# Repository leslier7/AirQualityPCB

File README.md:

# Air Quality PCB

A custom air quality monitoring device with an ESP32-C3 microcontroller, designed to measure environmental sensor data and transmit it over WiFi and LoRa.

## Repository Structure

```
AirQualityPCB/
├── PCB/        # KiCad schematic, layout, BOM, and fabrication outputs
└── Firmware/   # PlatformIO firmware for the ESP32-C3
```

## PCB

The PCB was designed in KiCad and lives in the [PCB/](PCB/) folder. This folder contains the schematic, board layout, and a custom component library (3D models, footprints, and symbols).

The BOM, STEP file, and Gerbers can be found on the [GitHub Releases](https://github.com/leslier7/AirQualityPCB/releases) page. They can also be extracted from the KiCAD project.

## Firmware

The firmware is written in C++ using the PlatformIO build system and targets the ESP32-C3.

For instructions on setting up the development environment, building, and flashing the firmware, see [Firmware/README.md](Firmware/README.md).

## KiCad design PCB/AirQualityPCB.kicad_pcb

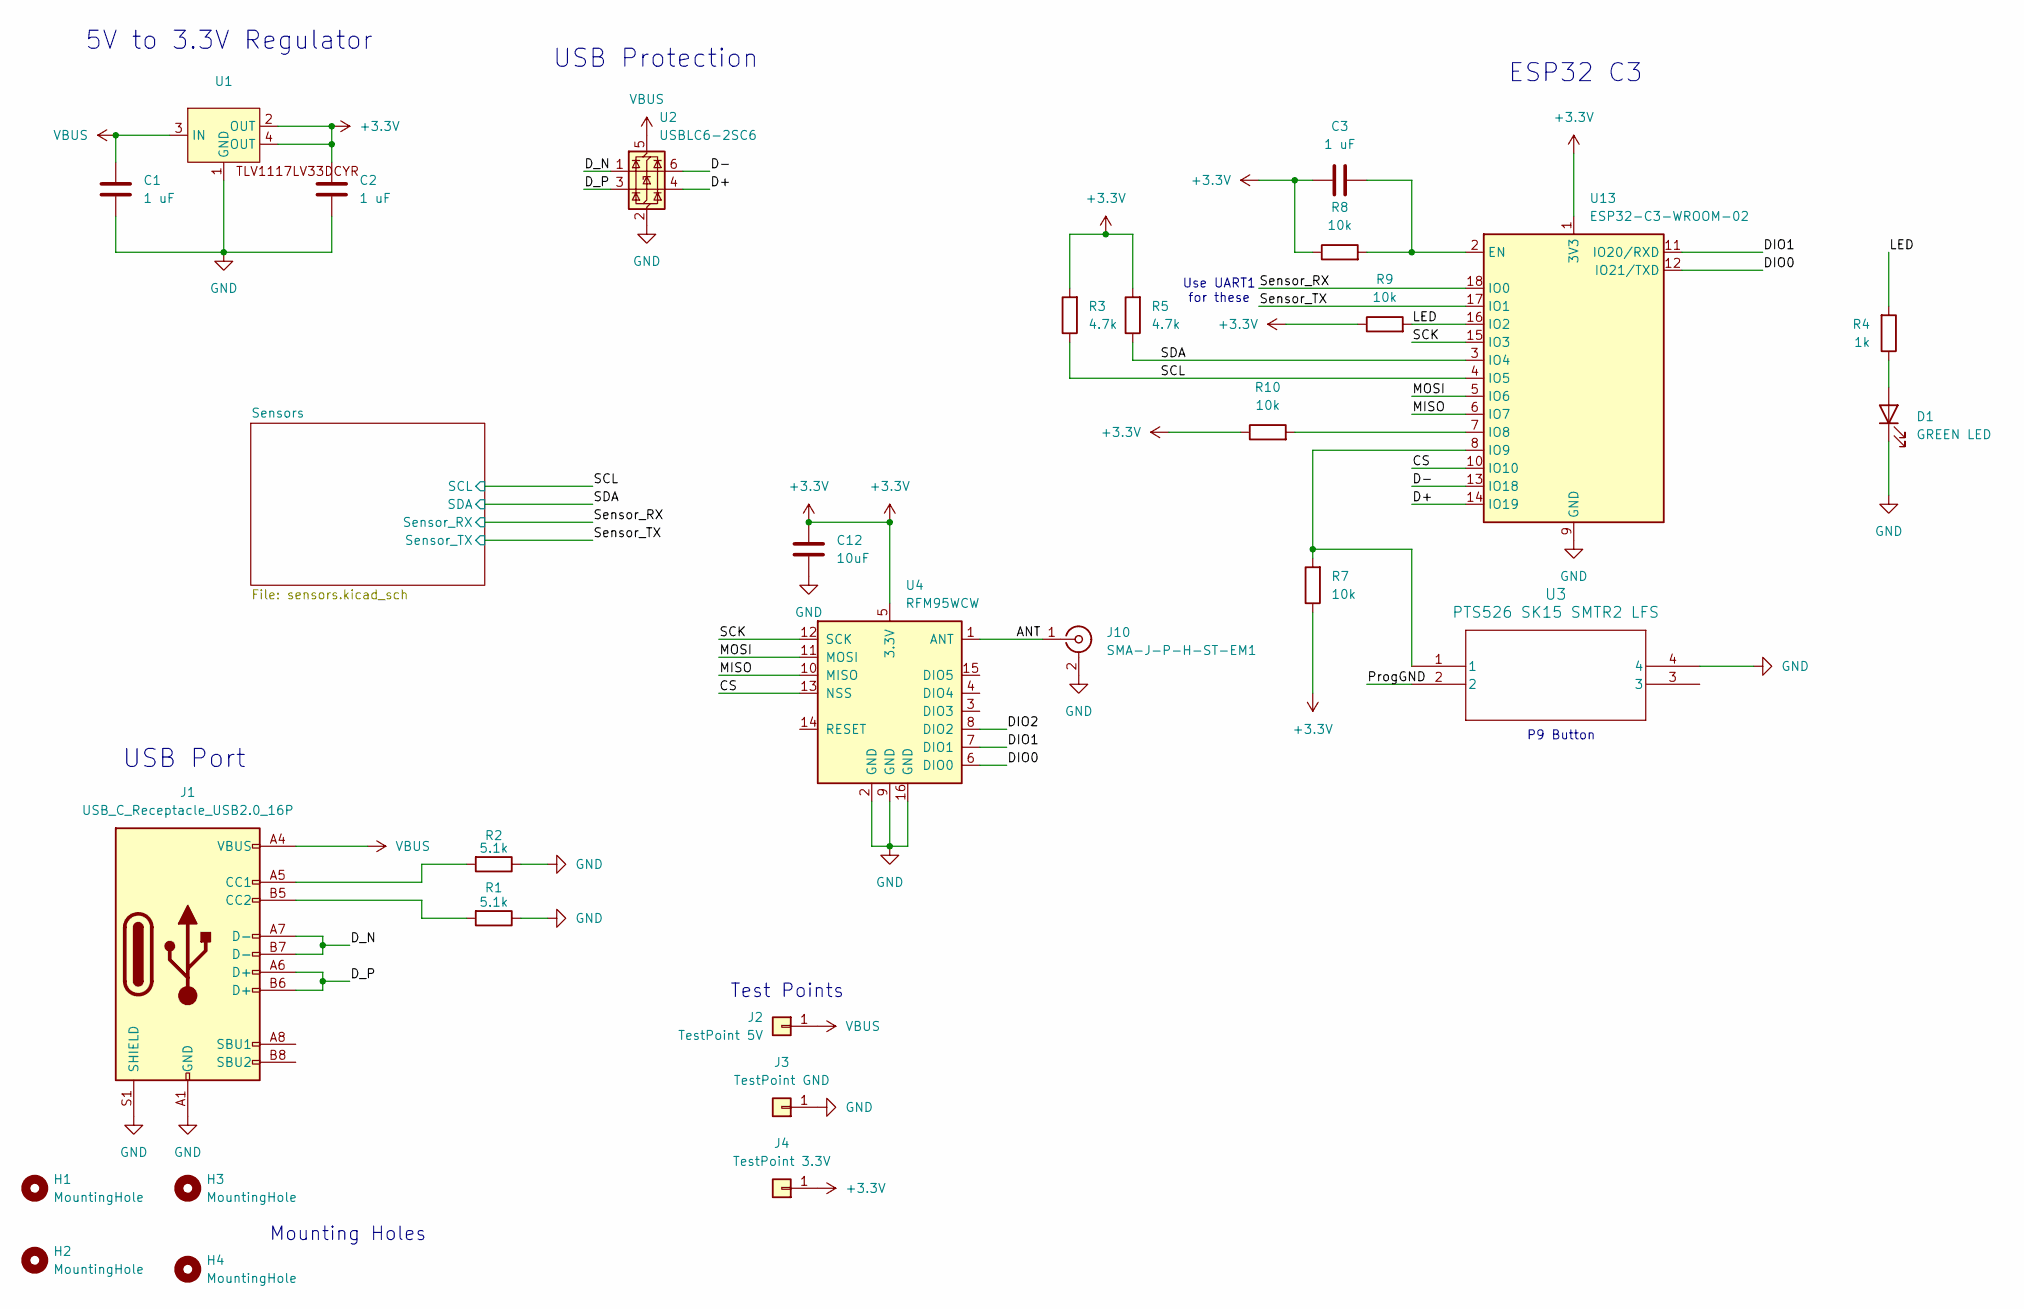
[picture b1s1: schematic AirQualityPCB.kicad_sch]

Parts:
C1, C2, C3: 1 uF; C_1206_3216Metric; Manufacturer Part Number CL31B105KCHNNNE
C12: 10uF; C_1206_3216Metric; Manufacturer Part Number TMK316BJ106KL-T
D1: GREEN LED; LED_1206_3216Metric; Manufacturer Part Number HSMG-C150
H1, H2, H3, H4: MountingHole; MountingHole_3.2mm_M3_ISO7380_Pad
J1: USB_C_Receptacle_USB2.0_16P; USB_C_Receptacle_GCT_USB4105-xx-A_16P_TopMnt_Horizontal; Manufacturer Part Number USB4105-GF-A
J2: TestPoint 5V; TestPoint_Pad_D1.0mm
J3: TestPoint GND; TestPoint_Pad_D1.0mm
J4: TestPoint 3.3V; TestPoint_Pad_D1.0mm
J10: SMA-J-P-H-ST-EM1; SMA_Samtec_SMA-J-P-H-ST-EM1_EdgeMount; Manufacturer Part Number SMA-J-P-H-ST-EM1
R1, R2: 5.1k; R_1206_3216Metric; Manufacturer Part Number CRCW12065K10FKEA
R3, R5: 4.7k; R_1206_3216Metric; Manufacturer Part Number RT1206FRE074K7L
R4: 1k; R_1206_3216Metric; Manufacturer Part Number RC1206FR-071KL
R7, R8, R9, R10: 10k; R_0805_2012Metric; Manufacturer Part Number RR1220P-103-D
U1: Regulator; SOT-223; Manufacturer Part Number TLV1117LV33DCYR
U2: USBLC6-2SC6; SOT-23-6; Manufacturer Part Number USBLC6-2SC6
U3: PTS526 SK15 SMTR2 LFS; PTS526SK15SMTR2 LFS; Manufacturer Part Number PTS526SK15SMTR2 LFS
U4: RFM95WCW; HOPERF_RFM9XW_SMD; Manufacturer Part Number COM-18085
U13: ESP32-C3-WROOM-02; Manufacturer Part Number ESP32-C3-WROOM-02-N4

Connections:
+3.3V: C2.2, C3.1, C12.2, J4.1, R3.2, R5.2, R7.1, R8.1, R9.1, R10.1, U1.2 (OUT), U1.4 (OUT), U4.5 (3.3V), U13.1 (3V3); also elsewhere on the board
/ANT: J10.1 (In), U4.1 (ANT)
/CS: U4.13 (NSS), U13.10 (IO10)
/D+: U2.4 (I/O2), U13.14 (IO19)
/D-: U2.6 (I/O1), U13.13 (IO18)
/DIO0: U4.6 (DIO0), U13.12 (IO21/TXD)
/DIO1: U4.7 (DIO1), U13.11 (IO20/RXD)
/DIO2: U4.8 (DIO2)
/D_N: J1.A7 (D-), J1.B7 (D-), U2.1 (I/O1)
/D_P: J1.A6 (D+), J1.B6 (D+), U2.3 (I/O2)
/LED: R4.2, R9.2, U13.16 (IO2)
/MISO: U4.10 (MISO), U13.6 (IO7)
/MOSI: U4.11 (MOSI), U13.5 (IO6)
/ProgGND: U3.2
/SCK: U4.12 (SCK), U13.15 (IO3)
/SCL: R3.1, U13.4 (IO5); also elsewhere on the board
/SDA: R5.1, U13.3 (IO4); also elsewhere on the board
/Sensor_RX: U13.18 (IO0); also elsewhere on the board
/Sensor_TX: U13.17 (IO1); also elsewhere on the board
GND: C1.1, C2.1, C12.1, D1.1 (K), J1.A1 (GND), J1.A12 (GND), J1.B1 (GND), J1.B12 (GND), J1.S1 (SHIELD), J3.1, J10.2 (Ext), R1.1, R2.1, U1.1 (GND), U2.2 (GND), U3.4, U4.2 (GND), U4.9 (GND), U4.16 (GND), U13.9 (GND), U13.19 (GND); also elsewhere on the board
unnamed: D1.2 (A), R4.1
unnamed: J1.A5 (CC1), R2.2
unnamed: J1.B5 (CC2), R1.2
unnamed: C3.2, R8.2, U13.2 (EN)
unnamed: R10.2, U13.7 (IO8)
unnamed: R7.2, U3.1, U13.8 (IO9)
VBUS: C1.2, J1.A4 (VBUS), J1.A9 (VBUS), J1.B4 (VBUS), J1.B9 (VBUS), J2.1, U1.3 (IN), U2.5 (VBUS)

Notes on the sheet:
USB Protection
5V to 3.3V Regulator
Test Points
Use UART1 for these
Mounting Holes
P9 Button
ESP32 C3
USB Port

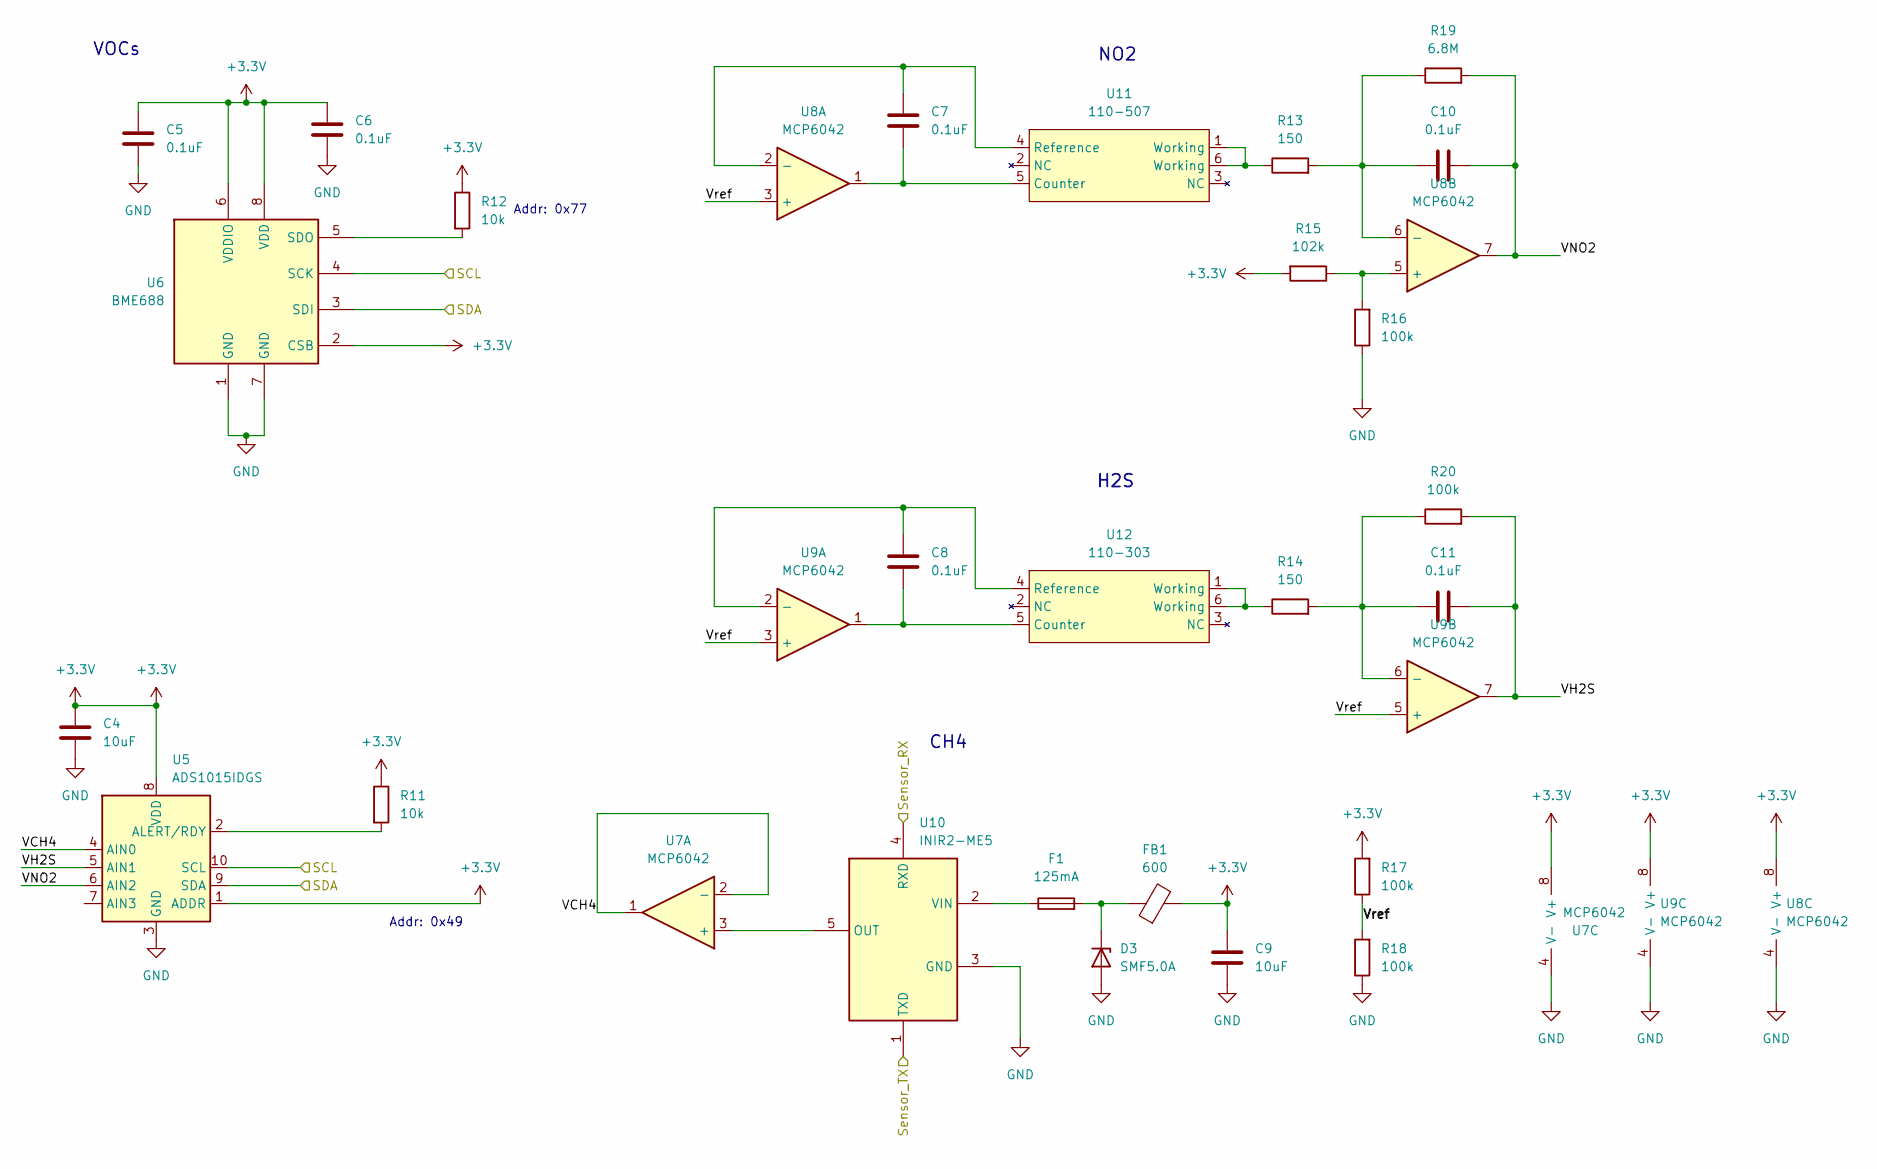
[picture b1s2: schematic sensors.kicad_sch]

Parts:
C4, C9: 10uF; C_1206_3216Metric; Manufacturer Part Number TMK316BJ106KL-T
C5, C6, C7, C8, C10, C11: 0.1uF; C_0805_2012Metric; Manufacturer Part Number C0805F104K1RACAUTO
D3: SMF5.0A; D_SOD-123; Manufacturer Part Number SMF5.0A
F1: 125mA; Fuse_1206_3216Metric; Manufacturer Part Number 0466.125NRHF
FB1: 600; L_1206_3216Metric; Manufacturer Part Number 742792133
R11, R12: 10k; R_0805_2012Metric; Manufacturer Part Number RR1220P-103-D
R13, R14: 150; R_0603_1608Metric; Manufacturer Part Number ERA-3AEB151V
R15: 102k; R_0603_1608Metric; Manufacturer Part Number RC0603FR-07102KL
R16, R17, R18, R20: 100k; R_0603_1608Metric; Manufacturer Part Number RC0603FR-07100KL
R19: 6.8M; R_0603_1608Metric; Manufacturer Part Number RC0603JR-076M8L
U5: ADS1015IDGS; TSSOP-10_3x3mm_P0.5mm; Manufacturer Part Number ADS1015IDGSR
U6: BME688; Bosch_LGA-8_3x3mm_P0.8mm_ClockwisePinNumbering; Manufacturer Part Number BME688
U7, U8, U9: MCP6042; SOIC-8_3.9x4.9mm_P1.27mm; Manufacturer Part Number MCP6042T-I/SN
U10: INIR2-ME5; INIR2ME5; Manufacturer Part Number INIR2-ME5
U11: 110-507; 110-Footprint; Manufacturer Part Number 110-507
U12: 110-303; 110-Footprint; Manufacturer Part Number 110-303

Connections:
+3.3V: C4.1, C5.1, C6.1, C9.1, FB1.2, R11.1, R12.1, R15.2, R17.2, U5.1 (ADDR), U5.8 (VDD), U6.2 (CSB), U6.6 (VDDIO), U6.8 (VDD), U7.8 (V+), U8.8 (V+), U9.8 (V+); also elsewhere on the board
/SCL: U5.10 (SCL), U6.4 (SCK); also elsewhere on the board
/SDA: U5.9 (SDA), U6.3 (SDI); also elsewhere on the board
/Sensor_RX: U10.4 (RXD); also elsewhere on the board
/Sensor_TX: U10.1 (TXD); also elsewhere on the board
/Sensors/VCH4: U5.4 (AIN0), U7.1, U7.2 (-)
/Sensors/VH2S: C11.2, R20.2, U5.5 (AIN1), U9.7
/Sensors/VNO2: C10.2, R19.2, U5.6 (AIN2), U8.7
/Sensors/Vref: R17.1, R18.2, U8.3 (+), U9.3 (+), U9.5 (+)
GND: C4.2, C5.2, C6.2, C9.2, D3.2 (A), R16.1, R18.1, U5.3 (GND), U6.1 (GND), U6.7 (GND), U7.4 (V-), U8.4 (V-), U9.4 (V-), U10.3 (GND); also elsewhere on the board
unnamed: D3.1 (K), F1.2, FB1.1
unnamed: R13.1, U11.1 (Working), U11.6 (Working)
unnamed: R14.1, U12.1 (Working), U12.6 (Working)
unnamed: R11.2, U5.2 (ALERT/RDY)
unnamed: R12.2, U6.5 (SDO)
unnamed: R15.1, R16.2, U8.5 (+)
unnamed: C10.1, R13.2, R19.1, U8.6 (-)
unnamed: C11.1, R14.2, R20.1, U9.6 (-)
unnamed: U7.3 (+), U10.5 (OUT)
unnamed: F1.1, U10.2 (VIN)
unnamed: C7.2, U8.1, U11.5 (Counter)
unnamed: C7.1, U8.2 (-), U11.4 (Reference)
unnamed: C8.2, U9.1, U12.5 (Counter)
unnamed: C8.1, U9.2 (-), U12.4 (Reference)

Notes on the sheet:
NO2
H2S
Addr: 0x49
CH4
Addr: 0x77
VOCs

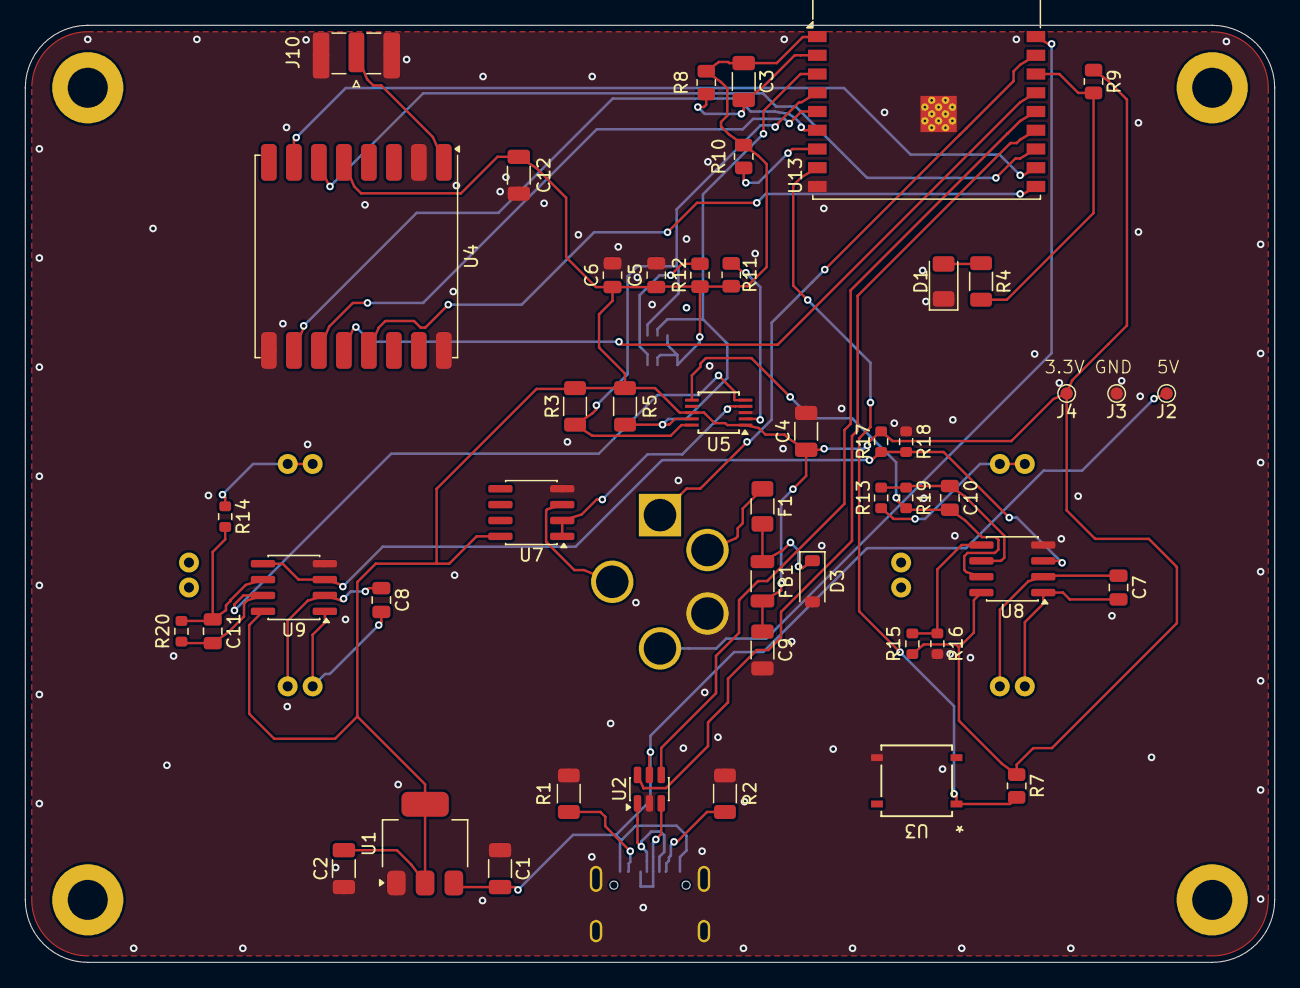
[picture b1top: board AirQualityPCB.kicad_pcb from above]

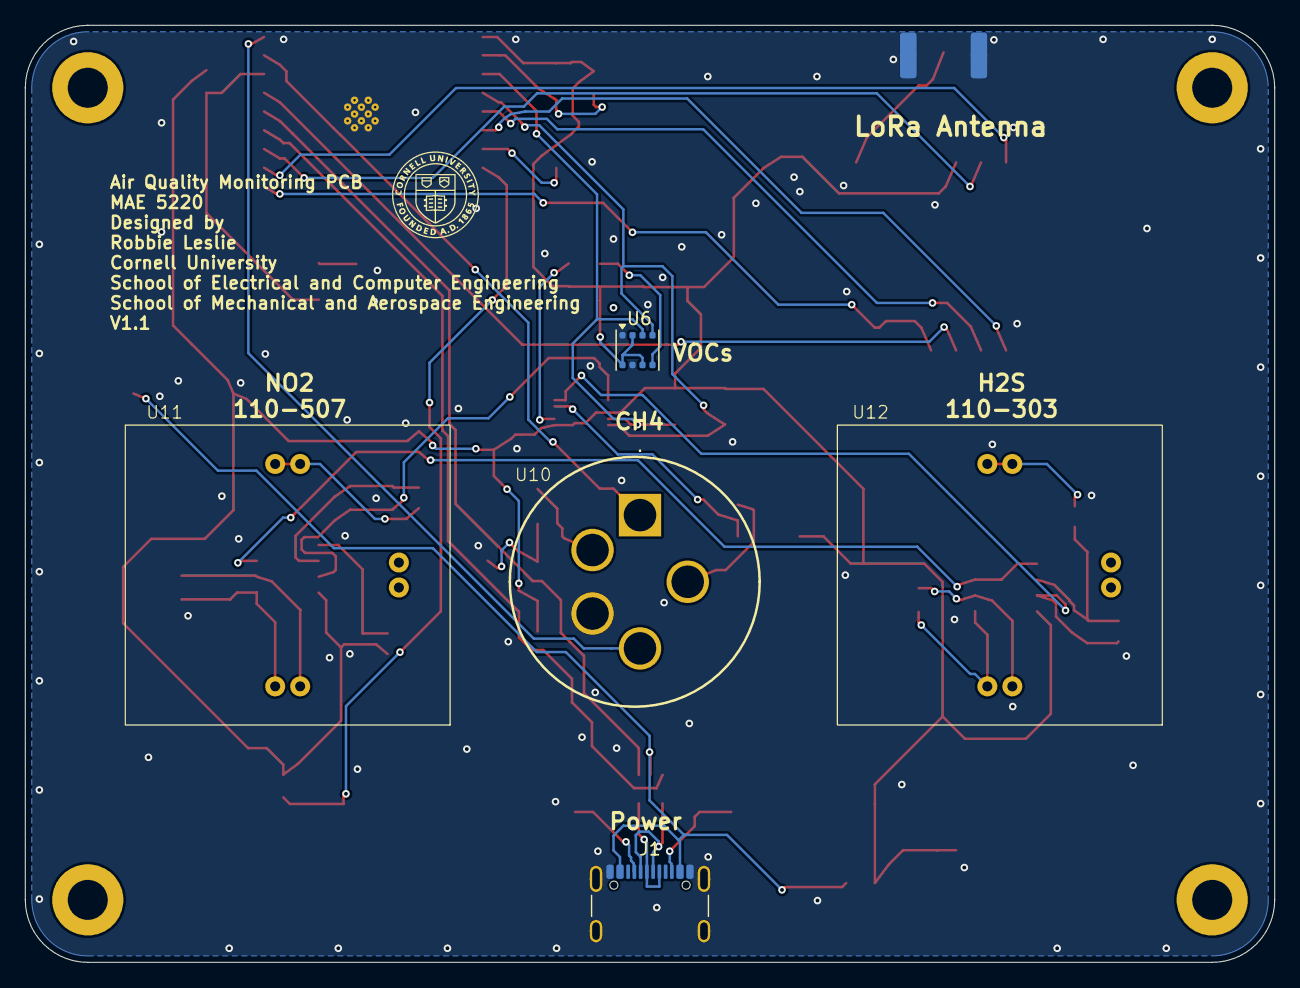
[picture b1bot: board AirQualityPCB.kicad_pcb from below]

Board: 2 copper layers, 100.0 x 75.0 mm, 57 parts (5 on the bottom side), 43 nets.

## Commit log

2026-03-21 Started working on PCB
2026-03-22 Finished schematic
2026-03-23 Finished first footprint (no routing)
2026-03-23 Updated silkscreen
2026-03-25 Before routing
2026-03-25 Removed components pre quilter routing
2026-03-26 v1.0 done
2026-03-26 Fabrication
2026-04-06 Moved PCB into subfolder and started work on firmware
2026-04-12 Updated gitignore
2026-04-13 Fixed op amp short bug
2026-04-13 Swapped LED to pin 2
2026-04-13 Swapped USB CC resistors
2026-04-14 Switched sockets, fixed USB, and SPI test
2026-04-14 Got LoRa working
2026-04-14 Started work on collecting data from sensors
2026-04-14 Updated fuse and started work on talking with CH4 sensor
2026-04-23 Continued work on firmware
2026-04-27 Continued work on reading sensors
2026-04-28 Got Ch4 reading working
2026-04-29 Working on firmware
2026-05-01 More work on the firmware
2026-05-12 Fixed too frequent downlinks
2026-05-12 Disabling downlinking since we dont need it
2026-05-13 Added top level README
2026-05-14 Fixed H2S offset bug
